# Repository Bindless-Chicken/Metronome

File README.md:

<h1 align=center>
   
    <br>
    Metronome
    <br>
    <br>
    <a href="https://oshpark.com/shared_projects/o1i7L0Sa"></img></a>
</h1>

## Theory of operation
The board is designed only around basic logic chips, hence why you won't find any microcontrollers here. The circuit can be split into two sub-circuits, the tune generation, and the pulse generation.

### Tune generation
To act as a proper metronome, we needed to have two different tune: one for the first pulse and a second for the other three. Tune generation is done using a NE555 *U1* which output is fed into a 74HC163 *U3* counter. The counter in that case is acting as a frequency divider, dividing the 2kHz output of the astable 555 timer into a 1kHz signal and a 500Hz one.

Effectively, at the end of the tune generator we are left with to square waves at 1kHz and 500Hz, which are respectively a C5 and a C6.

### Pulse generation
Once again a NE555 *U2* astable timer is used to generate the pulsation, using a potentiometer the output frequency can be changed between 0.53Hz and 3.47Hz, effectively changing the tempo between 40 BPM and 208 BPM.

The output of the timer is fed into a CD4017 *U4* Johnson counter. The output of the counter are the four outputs P1, P2, P3, and P4 triggering in order, one after another.

A shorter pulse is generated in order to have a more punchy effect on the pulse. This is done by reducing the original pulse duration using a RC delay line *U7*.

### Putting it all together
For silent operation, four LEDs have been put at the top, they are directly wired to the Johnson counter outputs.

To get the right sound at the right time, the tunes generated previously are `and` *U6* with their respective pulse; high pitch with the first output and low pitch with the others. For optimization sake, the other three are `and` *U6* with the `not` *U5* of the first pulse. Finally, all the signaled are put together using an `or` *U8*.

## BOM

| Reference      |  Value          |  Footprint                                        |
|----------------|-----------------|---------------------------------------------------|
| U1, U2         | NE555           | SOIC-8 3.9x4.9mm Pitch 1.27mm                     |
| U3             | 74HC16          | SOIC-16_3.9x9.9mm Pitch 1.27mm                    |
| U4             | CD4017          | SOIC-16 3.9x9.9mm Pitch 1.27mm                    |
| U5             | MC74VHC1GU04    | SOT-23-5                                          |
| U6             | 74LS08          | SOIC-14 3.9x8.7mm Pitch 1.27mm                    |
| U7             | SN74LVC1G08     | SOT-23-5                                          |
| U8             | SN74LVC1G32     | SOT-23-5                                          |
| R1             | 330             | 0805                                              |
| R2, R3, R4     | 91              | 0805                                              |
| R5, R6, R7     | 5.1k            | 0805                                              |
| R8             | 12k             | 0805                                              |
| R9             | 10k             | 0805                                              |
| C1             | 47nF            | 0805                                              |
| C2             | 10uF            | 0805                                              |
| C3, C4, C5, C6 | 10nF            | 0805                                              |
| C7             | 1uF             | 0805                                              |
| D1             | Red             | LED D5.0mm                                        |
| D2, D3, D4     | Green           | LED D5.0mm                                        |
| RV1            | 100k            | Trimmer Vishay TS53YL                             |
| P1             | USB_OTG         | 10118193-0001LF                                   |

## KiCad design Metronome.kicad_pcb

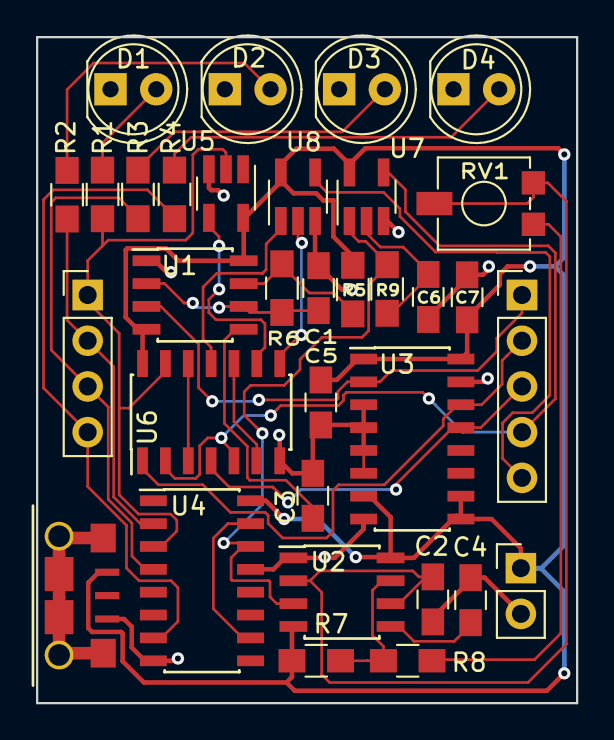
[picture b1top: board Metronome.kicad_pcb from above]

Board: 2 copper layers, 30.0 x 37.0 mm, 33 parts (0 on the bottom side), 30 nets.

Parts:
C1: 47nF; C_0805_HandSoldering
C2: 10uF; C_0805_HandSoldering
C3, C4, C5: 10nF; C_0805_HandSoldering
C6: 0.01uF; C_0805_HandSoldering
C7: 1uF; C_0805_HandSoldering
D1: Red; LED_D5.0mm
D2, D3, D4: Green; LED_D5.0mm
P1: USB_OTG; 10118193-0001LF
P2: CONN_01X02; Socket_Strip_Straight_1x02_Pitch2.54mm
P3: CONN_01X05; Socket_Strip_Straight_1x05_Pitch2.54mm
P4: CONN_01X04; Socket_Strip_Straight_1x04_Pitch2.54mm
R1: 330; R_0805_HandSoldering
R2, R3, R4: 91; R_0805_HandSoldering
R5, R6, R7: 5.1k; R_0805_HandSoldering
R8: 12k; R_0805_HandSoldering
R9: 10k; R_0805_HandSoldering
RV1: 100k; Potentiometer_Trimmer_Vishay_TS53YL
U1, U2: NE555; SOIC-8_3.9x4.9mm_Pitch1.27mm
U3: 74HC163; SOIC-16_3.9x9.9mm_Pitch1.27mm
U4: CD4017; SOIC-16_3.9x9.9mm_Pitch1.27mm
U5: MC74VHC1GU04; SOT-23-5_HandSoldering
U6: 74LS08; SOIC-14_3.9x8.7mm_Pitch1.27mm
U7: SN74LVC1G08; SOT-23-5_HandSoldering
U8: SN74LVC1G32; SOT-23-5_HandSoldering

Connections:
/Output: P3.5, U8.4
/P1: P4.1, R1.1, U4.3, U5.2, U6.13
/P2: P4.2, R2.1, U4.2
/P3: P4.3, R3.1, U4.4
/P4: P4.4, R4.1, U4.7
/Pulse: P3.4, U6.2, U6.5, U7.4
/f1: P3.1, U1.3, U3.2
/f2: P3.2, U3.14, U6.1
/f3: P3.3, U3.13, U6.4
/f4: R9.2, U2.3, U4.14, U7.1
GND: C1.2, C2.2, C3.2, C4.2, C5.2, C6.2, C7.2, D1.1, D2.1, D3.1, D4.1, P1.5, P2.2, U1.1, U2.1, U3.3, U3.4, U3.5, U3.6, U3.8, U3.15, U4.8, U4.13, U5.3, U6.7, U7.3, U8.3
unnamed: C1.1, R6.2, U1.2, U1.6
unnamed: C2.1, RV1.1, RV1.2, U2.2, U2.6
unnamed: C3.1, U1.5
unnamed: C4.1, U2.5
unnamed: C6.1, R9.1, U7.2
unnamed: D1.2, R1.2
unnamed: D2.2, R2.2
unnamed: D3.2, R3.2
unnamed: D4.2, R4.2
unnamed: R5.2, R6.1, U1.7
unnamed: R7.2, R8.1, U2.7
unnamed: R8.2, RV1.3
unnamed: U4.10, U4.15
unnamed: U5.4, U6.9
unnamed: U6.8, U8.2
unnamed: U6.6, U6.10
unnamed: U6.11, U8.1
unnamed: U6.3, U6.12
VCC: C5.1, C7.1, P1.1, P2.1, R5.1, R7.1, U1.4, U1.8, U2.4, U2.8, U3.1, U3.7, U3.9, U3.10, U3.16, U4.16, U5.5, U6.14, U7.5, U8.5

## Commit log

2018-02-09 Gerber export
2018-02-09 Improve readme
2018-02-09 Add schematics export
